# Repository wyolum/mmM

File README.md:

# mmMercury
mmMercury is an Open Hardware, blood pressure measurement device (not FDA approved).
=======

License
-------
[CERN Open Hardware Licence v1.2 ]

[CERN Open Hardware Licence v1.2 ]:http://www.ohwr.org/attachments/2388/cern_ohl_v_1_2.txt

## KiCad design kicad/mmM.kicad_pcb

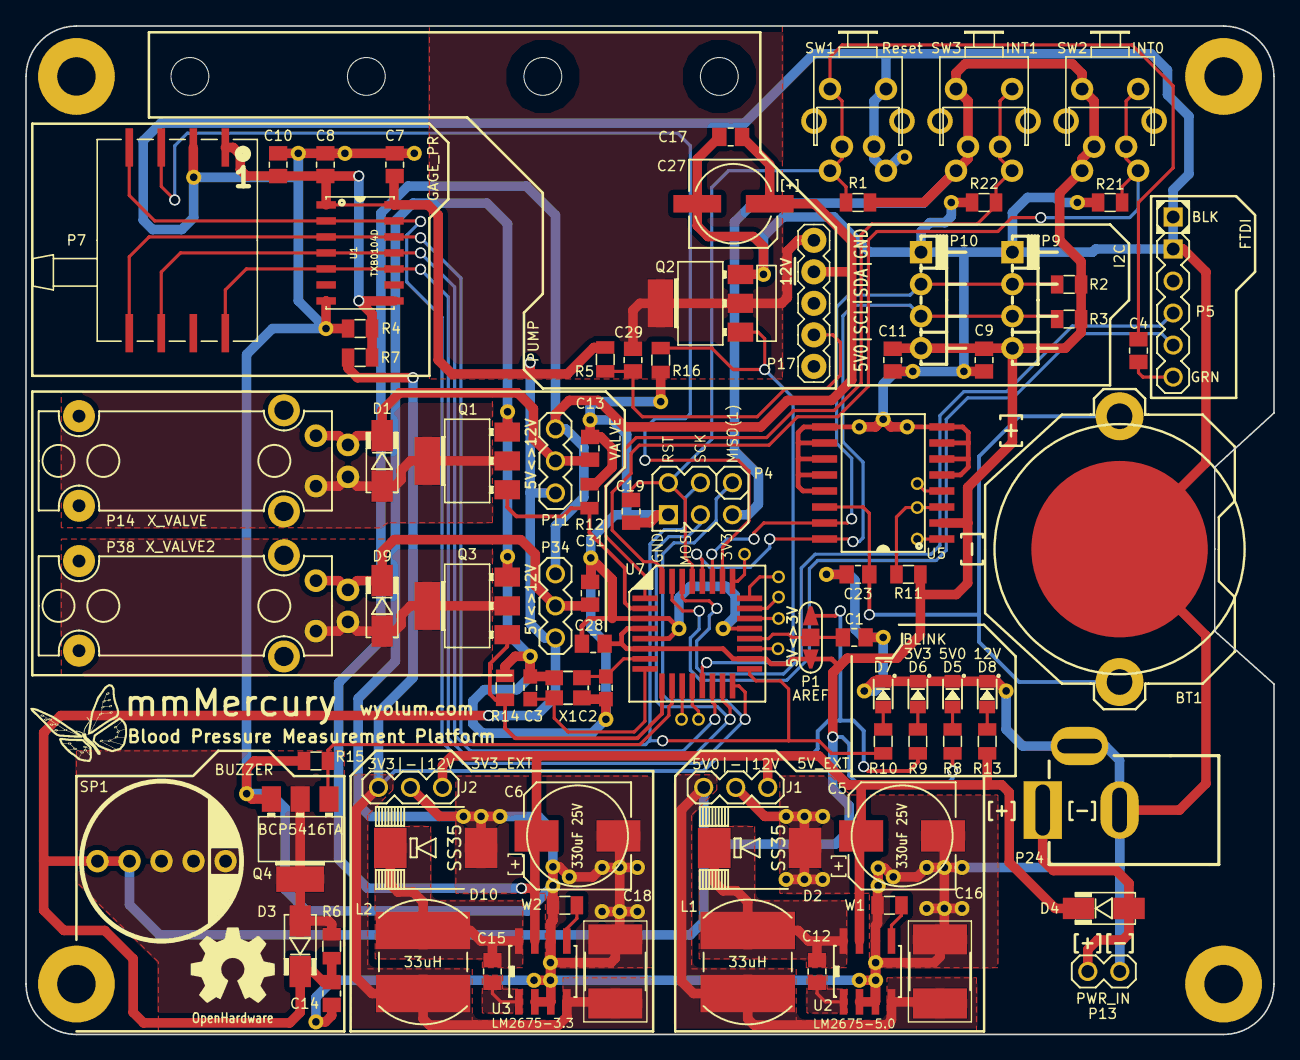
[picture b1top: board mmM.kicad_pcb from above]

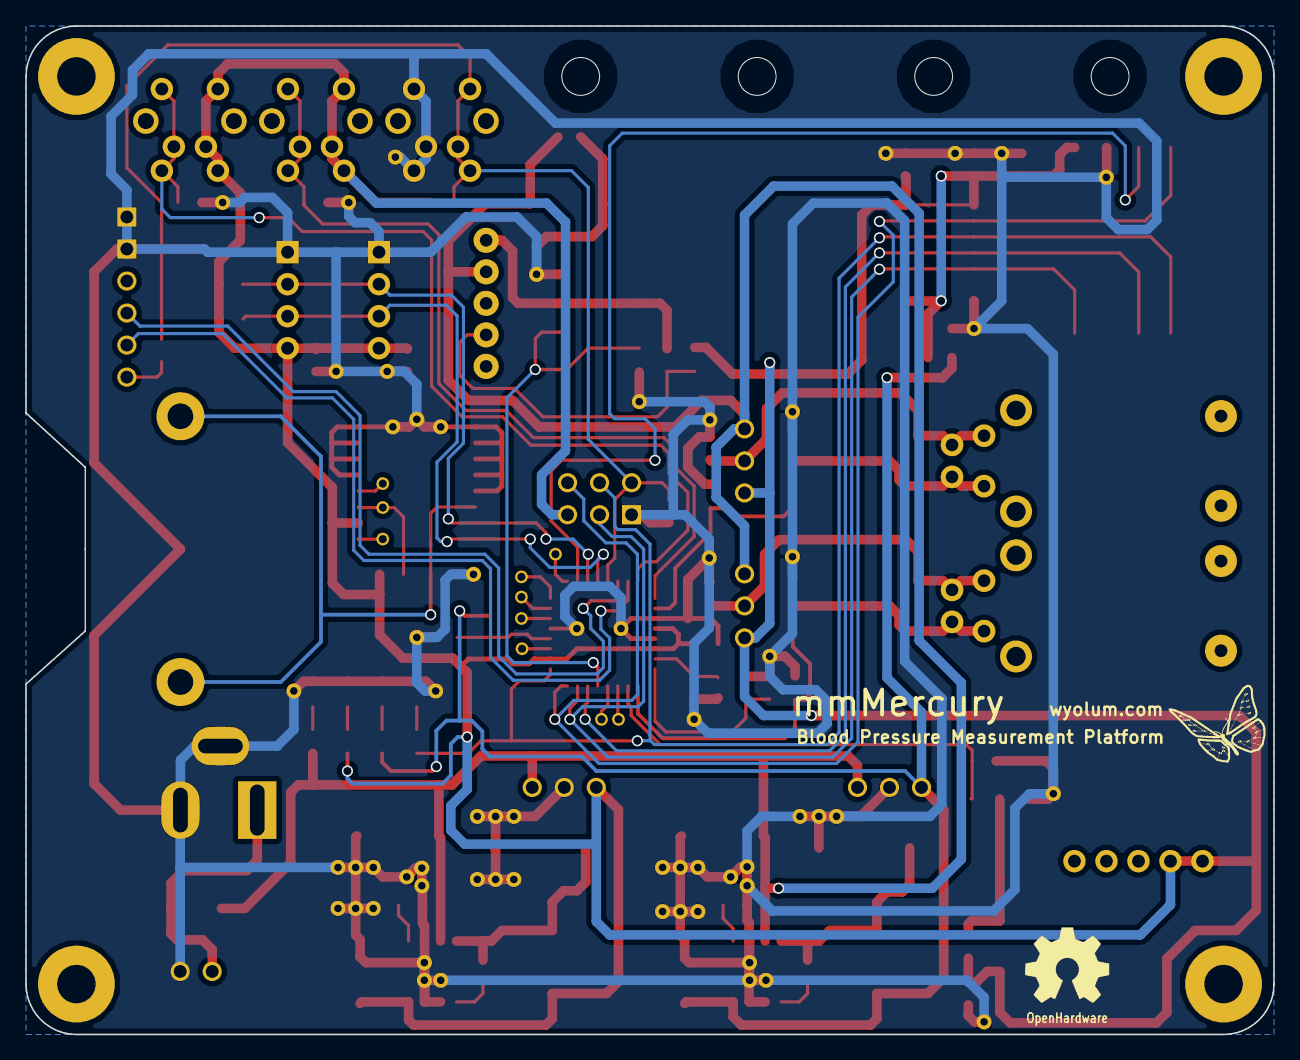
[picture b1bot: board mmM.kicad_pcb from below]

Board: 2 copper layers, 99.0 x 80.0 mm, 167 parts (2 on the bottom side), 53 nets.

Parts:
B1, B2, B3: I_O
B4, B12: PB0; I_O
B7, B9: PC1; I_O
B8: PC0; I_O
B10: PC6; I_O
B11: PC7; I_O
BT1: BATT_HOLDER; CR2032
C1, C4, C7, C8, C9, C10, C11, C13, C14, C17, C19, C23, C28, C29, C31: 100nF; c_0805
C2, C3: 22pF; c_0603
C5, C6: 330uF 25V; C_ELCO_SMD_8x10
C12, C15: 10nF; c_0805
C16, C18: 100uF 10V; C_2917_HandSoldering
C27: 100uF; C_ELCO_SMD
D1, D3, D4, D9: ES1D-13-F; diode-DO214AC
D2, D10: SS35; DO-214AB
D5: 5V0; led_0805
D6: 3V3; led_0805
D7: BLINK; led_0805
D8: 12V; led_0805
G1, G2: Logo_Wyolum; Logo-WL3
G3, G3#2, G4: Logo_OH; OSHW_6mm
J1: 5V_EXT; Header_3
J2: 3V3_EXT; Header_3
L1, L2: 33uH; Choke_SMD_Wuerth-784775133
P1: AREF; ShortLink2
P4: ICSP; Header_ISP
P5: FTDI; Header_FTDI
P7: GAGE_PR; HCEM500GUH9P3
P9, P10: C3SB; pin_strip_4-90
P11: VSel_Vlv; Header_3
P13: PWR_IN; Header_2
P14: X_VALVE; X_Valve_2
P17: PUMP; Pump_P54E01R_03
P24: PWR_IN; JACK_ALIM
P34: VSel_Vlv2; Header_3
P38: X_VALVE2; X_Valve_2
Q1, Q2, Q3, Q4: BCP5416TA; SOT223
R1, R2, R3, R4, R11, R12, R14, R15, R16, R21, R22: 10k; r_0805
R5: 4k7; r_0805
R6, R10, R13: 1k; r_0805
R7: Zero; r_0805
R8: 330E; r_0805
R9: 120E; r_0805
REF1, REF2, REF3, REF4, REF5, REF6, REF7, REF8, REF9, REF10, REF11, REF12, REF13, REF14, REF15, REF16, REF17, REF18, REF19, REF20, REF21, REF22, REF23, REF24, REF25, REF26, REF27, REF55, REF56, REF57, REF58, REF60, REF61, REF62: via01
REF28, REF29, REF30, REF31, REF32, REF33, REF34, REF35, REF36, REF37, REF38, REF39, REF40, REF41, REF42, REF43, REF44, REF45, REF46, REF47, REF48, REF49, REF50, REF51, REF52, REF53, REF54, REF59: via01; via_th
SC6, SC7, SC9, SC10: SCREW; vite_3mm
SP1: BUZZER; Speaker
SW1: Reset; SW_PB_V_H
SW2: INT0; SW_PB_V_H
SW3: INT1; SW_PB_V_H
U1: TXB0104D
U2: LM2675-5.0; SO8E
U3: LM2675-3.3; SO8E
U5: DS3231N; DS3231
U7: ATMEGA328P-AU-ND; TQFP32
W1, W2: EN; r_0805
X1: 16MHz; Xtal_SMD3

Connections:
+3.3V: C18.1, J2.1, L2.2, P1.1, R7.1, R9.1, U3.4
/AREF: C1.1, P1.2, U7.20
/Interface/5V0: C7.1, C8.1, C9.1, C10.1, C11.1, C14.1, C16.1, C28.1, D3.2, J1.1, L1.2, P1.3, P4.2, P7.1, P9.1, P10.1, P11.1, P34.1, R1.1, R2.1, R3.1, R4.2, R5.1, R6.1, R7.2, R8.1, R11.1, SP1.1, SW2.2, SW3.2, U1.1, U1.8, U1.14, U2.4, U5.2, U7.4, U7.6, U7.18
/Interface/12V: C5.1, C6.1, C17.1, C27.1, D4.2, J1.3, J2.3, P11.3, P17.2, P34.3, R13.1, U2.7, U3.7
/Interface/+Vlv: C13.1, D1.2, P11.2, P14.2
/Interface/+Vlv2: C31.1, D9.2, P34.2, P38.2
/Interface/-Vlv: D1.1, P14.1, Q1.2
/Interface/-Vlv2: D9.1, P38.1, Q3.2
/Interface/MISO: P4.1, P7.4, U1.2, U1.13, U7.16
/Interface/PC3_Pr1: P7.3, U7.26
/Interface/PD4_Valve2: Q1.1, R12.1, U7.2
/Interface/Pump: C29.1, P17.4, R5.2
/Interface/Pump_Ret: C29.2, P17.1, Q2.2
/Interface/SCK: P4.3, P7.5, R10.1, U1.3, U1.12, U7.17
/Interface/SCL: P9.2, P10.2, R3.2, U5.16, U7.28
/Interface/SDA: P9.3, P10.3, R2.2, U5.15, U7.27
/Interface/Spk: D3.1, Q4.2, R6.2, SP1.2
/Interface/~MOSI: P4.4, P7.8, U1.5, U1.10, U7.15
/Interface/~PB1_Pump: Q2.1, R16.2, U7.13
/Interface/~PD5_Valve: Q3.1, R14.1, U7.9
/Interface/~PD6_Spk: Q4.1, R15.2, U7.10
/Interface/~SS: P7.6, U1.4, U1.11, U7.14
/PB0: B12.1, U7.12
/PB6: C2.1, U7.7, X1.1
/PB7: C3.1, U7.8, X1.2
/PC0: B8.1, U7.23
/PC1: B9.1, U7.24
/PC2: B7.1, U7.25
/PC6: B10.1, U7.19
/PC7: B11.1, U7.22
/PD2: R21.1, SW2.1, U7.32
/PD7: B4.1, U7.11
/RESET: C4.1, C19.1, P4.5, R1.2, SW1.2, U7.29
/RXD: P5.4, U7.30
/TXD: P5.5, U7.31
/pwr/CB3: C15.2, U3.1
/pwr/CB5: C12.2, U2.1
/pwr/PWR_IN: D4.1, P13.1, P24.1
/pwr/VSW3: C15.1, D10.2, L2.1, U3.8
/pwr/VSW5: C12.1, D2.2, L1.1, U2.8
/rtc/32k: B3.1, U5.1
/rtc/BAT: BT1.+, C23.1, U5.14
/rtc/RST: B2.1, U5.4
/rtc/SQR: B1.1, R11.2, U5.3
/~PD3: R22.1, SW3.1, U7.1
/~RTS: C4.2, P5.6
GND: BT1.-, C1.2, C2.2, C3.2, C5.2, C6.2, C7.2, C8.2, C9.2, C10.2, C11.2, C13.2, C14.2, C16.2, C17.2, C18.2, C19.2, C23.2, C27.2, C28.2, C31.2, D2.1, D5.2, D6.2, D7.2, D8.2, D10.1, J1.2, J2.2, P4.6, P5.1, P5.2, P7.2, P9.4, P10.4, P13.2, P24.2, P24.3, Q1.3, Q2.3, Q3.3, Q4.3, R4.1, R12.2, R14.2, R15.1, R16.1, R21.2, R22.2, REF1.1, REF2.1, REF3.1, REF4.1, REF5.1, REF6.1, REF7.1, REF8.1, REF9.1, REF10.1, REF11.1, REF12.1, REF13.1, REF14.1, REF15.1, REF16.1, REF17.1, REF18.1, REF19.1, REF20.1, REF21.1, REF22.1, REF23.1, REF24.1, REF25.1, REF26.1, REF27.1, REF28.1, REF29.1, REF30.1, REF31.1, REF32.1, REF33.1, REF34.1, REF35.1, REF36.1, REF37.1, REF38.1, REF39.1, REF40.1, REF41.1, REF42.1, REF43.1, REF44.1, REF45.1, REF46.1, REF47.1, REF48.1, REF49.1, REF50.1, REF51.1, REF52.1, REF53.1, REF54.1, REF55.1, REF56.1, REF57.1, REF58.1, REF59.1, REF60.1, REF61.1, REF62.1, SW1.1, U1.7, U2.2, U2.3, U2.6, U3.2, U3.3, U3.6, U5.5, U5.6, U5.7, U5.8, U5.9, U5.10, U5.11, U5.12, U5.13, U7.3, U7.5, U7.21, W1.2, W2.2, X1.3
unnamed: D5.1, R8.2
unnamed: D6.1, R9.2
unnamed: D7.1, R10.2
unnamed: D8.1, R13.2
unnamed: U2.5, W1.1
unnamed: U3.5, W2.1

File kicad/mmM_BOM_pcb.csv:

"Id";"Designator";"Package";"Quantity";"Designation";"Supplier and ref";
1;"REF62,REF61,REF60,REF1,REF2,REF3,REF4,REF5,REF6,REF7,REF8,REF9,REF10,REF11,REF12,REF13,REF14,REF15,REF16,REF17,REF18,REF19,REF20,REF21,REF22,REF23,REF24,REF25,REF26,REF27,REF55,REF56,REF57,REF58";"via01";34;"via01";;;
2;"REF59,REF28,REF29,REF30,REF31,REF32,REF33,REF34,REF35,REF36,REF37,REF38,REF39,REF40,REF41,REF42,REF43,REF44,REF45,REF46,REF47,REF48,REF49,REF50,REF51,REF52,REF53,REF54";"via_th";28;"via01";;;
3;"B7,B9";"I_O";2;"PC1";;;
4;"B1,B2,B3";"I_O";3;"I_O";;;
5;"B4,B12";"I_O";2;"PB0";;;
6;"B8";"I_O";1;"PC0";;;
7;"B10";"I_O";1;"PC6";;;
8;"B11";"I_O";1;"PC7";;;
9;"BT1";"CR2032";1;"BATT_HOLDER";;;
10;"D1,D3,D4,D9";"diode-DO214AC";4;"ES1D-13-F";;;
11;"D5";"led_0805";1;"5V0";;;
12;"D6";"led_0805";1;"3V3";;;
13;"D7";"led_0805";1;"BLINK";;;
14;"D8";"led_0805";1;"12V";;;
15;"P1";"ShortLink2";1;"AREF";;;
16;"P4";"Header_ISP";1;"ICSP";;;
17;"P5";"Header_FTDI";1;"FTDI";;;
18;"P9,P10";"pin_strip_4-90";2;"C3SB";;;
19;"P11";"Header_3";1;"VSel_Vlv";;;
20;"P13";"Header_2";1;"PWR_IN";;;
21;"P14";"X_Valve_2";1;"X_VALVE";;;
22;"P24";"JACK_ALIM";1;"PWR_IN";;;
23;"P34";"Header_3";1;"VSel_Vlv2";;;
24;"P38";"X_Valve_2";1;"X_VALVE2";;;
25;"Q1,Q2,Q3,Q4";"SOT223";4;"BCP5416TA";;;
26;"SC6,SC7,SC9,SC10";"vite_3mm";4;"SCREW";;;
27;"SP1";"Speaker";1;"BUZZER";;;
28;"SW1";"SW_PB_V_H";1;"Reset";;;
29;"SW2";"SW_PB_V_H";1;"INT0";;;
30;"SW3";"SW_PB_V_H";1;"INT1";;;
31;"U5";"DS3231";1;"DS3231N";;;
32;"U7";"TQFP32";1;"ATMEGA328P-AU-ND";;;
33;"X1";"Xtal_SMD3";1;"16MHz";;;
34;"G1,G2";"Logo-WL3";2;"Logo_Wyolum";;;
35;"G3,G4";"OSHW_6mm";2;"Logo_OH";;;
36;"R22,R21,R11,R4,R3,R2,R1,R12,R14,R15,R16";"r_0805";11;"10k";;;
37;"R13,R10,R6";"r_0805";3;"1k";;;
38;"R9";"r_0805";1;"120E";;;
39;"R8";"r_0805";1;"330E";;;
40;"R5";"r_0805";1;"4k7";;;
41;"C3,C2";"c_0603";2;"22pF";;;
42;"P17";"Pump_P54E01R_03";1;"PUMP";;;
43;"W1,W2";"r_0805";2;"EN";;;
44;"U3";"SO8E";1;"LM2675-3.3";;;
45;"U2";"SO8E";1;"LM2675-5.0";;;
46;"C15,C12";"c_0805";2;"10nF";;;
47;"C1,C4,C7,C8,C9,C10,C11,C13,C14,C17,C23,C28,C29,C31,C19";"c_0805";15;"100nF";;;
48;"C18,C16";"C_2917_HandSoldering";2;"100uF 10V";;;
49;"J1";"Header_3";1;"5V_EXT";;;
50;"J2";"Header_3";1;"3V3_EXT";;;
51;"C6,C5";"C_ELCO_SMD_8x10";2;"330uF 25V";;;
52;"L2,L1";"Choke_SMD_Wuerth-784775133";2;"33uH";;;
53;"R7";"r_0805";1;"Zero";;;
54;"U1";"TXB0104D";1;"TXB0104D";;;
55;"D10,D2";"DO-214AB";2;"SS35";;;
56;"C27";"C_ELCO_SMD";1;"100uF";;;
57;"P7";"HCEM500GUH9P3";1;"GAGE_PR";;;

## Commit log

2015-07-06 old files from uC_v3 imported
2015-07-09 uCm initial commit, work in progress
2015-07-12 uCm work in progress
2015-07-12 made standard directory structure
2015-07-12 uCm KISS version
2015-08-24 work in progress
2015-09-01 making some progress on the PCB
2015-09-02 layout, work in progress
2015-09-05 Board layout complete. Gerbers, PDF', BoM generated.
2015-12-06 changed power supply section
2015-12-07 power supply sections changed
2015-12-07 layout finalized, needs a check for errors
2015-12-08 some mods to PCB layout
2015-12-08 renamed uCm to mmM
2015-12-08 Fresh BOM for mmM
2015-12-09 added pull down resistors on microcontroller outputs
2015-12-09 mods to board layout
2015-12-10 PCB optimization
2015-12-12 clean up
2015-12-17 BoM and 3D render work in progress
2015-12-17 3D render work in progress
2015-12-19 trying to fix my mess
2015-12-19 fresh 3D renders
2015-12-27 added Cap across RST sw. Fresh Gerbers, PDF. Final v1 ready for prototype
2015-12-27 made a pretty schematic, fresh symbols
2015-12-29 new BoM format for seeed
2016-02-13 new pumpt mount
2016-02-13 pump_clamp update to get rid of overhang
2016-02-14 increase diameters by.5mm
2016-02-14 added reference from okenseiko
2016-02-15 Board test program initial commit
2016-02-16 schematic label errors corrected, Git issue #2
2016-02-17 mmM enclosure WIP
2016-02-20 add TI voltage translator datasheet
2016-02-20 add gauge pressure sensor test
2016-02-23 updated pump height above board in p_clamp
2016-03-07 add bp_sim, and other methods
2016-03-08 add bp sim function
2016-03-08 mmM version of uControl Firmware
2016-03-12 minor mod to pump_mount final creation
2016-03-13 add second valve control
2016-03-13 correct Valve 2 pin mistake
2016-03-13 added simple gui for MMF_2016
2016-03-13 minor update
2016-03-18 added tri-graph script
2016-03-25 add beginnings of flowmeter input adapter
2016-03-25 added bpc scripts
2016-04-01 added test code for Sensirion flow sensor
2016-04-02 bug fix
2016-04-06 integrated Sensirion flow meter
2016-04-29 added a bunch of files
2016-04-29 added missing file
2016-04-30 rapid release
2016-05-01 maintenence
2016-05-01 usb panel mount outline for laser cutting
2016-05-02 added 3D printed enclosure frame
2016-05-07 added dxf file
2016-05-07 added screw holes and conntoured edges to bottom
2016-05-07 added 4100 flow meter spec
2016-05-07 mounting holes for all components in a separate file
2016-05-09 added openings to case, saved in svg file
2016-05-10 update flow sensor footprint
2016-05-13 tweak to case
2016-05-13 increased acr thickness
2016-07-11 added pygame based control panel
2016-07-14 made smaller background for pocket chip
2016-07-14 only initializeing display and font for pylab. Alsa was giving errors
2016-07-14 fixed background
2016-07-15 first version on pocket chip
2016-07-16 working on BP calc
2016-07-16 copied util.py from arduino/mmmControl2
2016-07-16 first printed BP run success!
2016-07-16 rudamentary BP integrated
2016-07-31 fixed bug with valves. LEDs now correspond to mmM_control status packets.
2016-07-31 moved gage text to center of dial.
2016-08-13 added an sqlite3 database module for recording results
2016-08-13 added time to BP results
2016-08-13 bugfix
2016-08-14 changed 'patient' to 'user'
2016-08-14 integrated user data to main gui
2016-08-19 added map and hr to results table
2016-08-19 cleaned up with pylint
2016-08-19 added eztext library and examples
2017-02-04 increased max pressure to 300 mmHG
2017-02-04 added data archiveing feature
2017-04-01 add honeywell zephyr datasheet
2017-04-01 added code to support Honeywell flow sensor
2017-04-01 added support for honeywell flow meter
2017-04-01 starting in vitro code
2017-04-01 create utility import directory
2017-04-01 adapt to utility python library structure
2017-04-01 update control panel app for util python directory
2017-04-01 ignore bad data from honeywell sensor
2017-04-01 added InVitro.py test
2017-04-02 add liquid pressure sensor support
2017-04-02 found bug in mmM control (liquid pressure) address
2017-04-02 add liquid pressure sensor datasheets
2017-04-02 adjusted number of taps to 1000 and brought low low pass cuttoff down to .1 Hz
2017-05-12 debugging checksum
2017-05-13 debugging compliance code
2017-06-20 added variable hold script
2017-08-06 comment out debug code, and report proper counts from the flow sensor
2018-03-31 added honeywell flow sensor to drive.py
2020-02-22 add i2c pressure sensor data sheet
2020-02-24 Liquid pressure example, and HardWire library
2026-05-02 Migrate uControl suite to Python 3
    - Apply 2to3 conversions (print functions, dict items, xrange)
    - Fix packet alignment and synchronization logic in drive.py
    - Resolve numpy sum() TypeError by coercing byte slice to integer list
    - Fix ShortPID %x formatting TypeError with ord()
    - Update pickle.dump to use binary write mode ('wb')
2026-05-04 addeed new GUIs
2026-05-10 Update drive.py: remove LengthError debug spam and add dynamic FTDI port discovery for macOS
2026-05-16 added pump rate commands.
2026-05-17 made change to keep valves open by default
2026-06-07 mmM update for kicad 10
2026-06-07 bard convert to ver 10

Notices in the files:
kicad/mmM.kicad_pcb:
This documentation describes Open Hardware and is licensed
under the CERN OHL v. 1.2. You may redistribute and modify
this documentation under the terms of the CERN OHL v.1.2.
